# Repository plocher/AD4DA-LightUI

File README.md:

View this project on [CADLAB.io](https://cadlab.io/project/2385). 

# AD4DA-LightUI
## License: CERN Open Hardware Licence v1.2

## Status: mature

4x slide potentiometers for use with I2C-AD4DA.

The Light UI has 4x slide potentiometers which are used to control
LED Layout lighting color balances and levels. It is designed to
connect to my I2C-AD4DA (I2C 4x Analog to Digital and 1x Digital
to Analog) interface board with an RJ45/8 connection.

## Versions:
 * 1.0
 * 2.0
 * 2.1
 * 2.2

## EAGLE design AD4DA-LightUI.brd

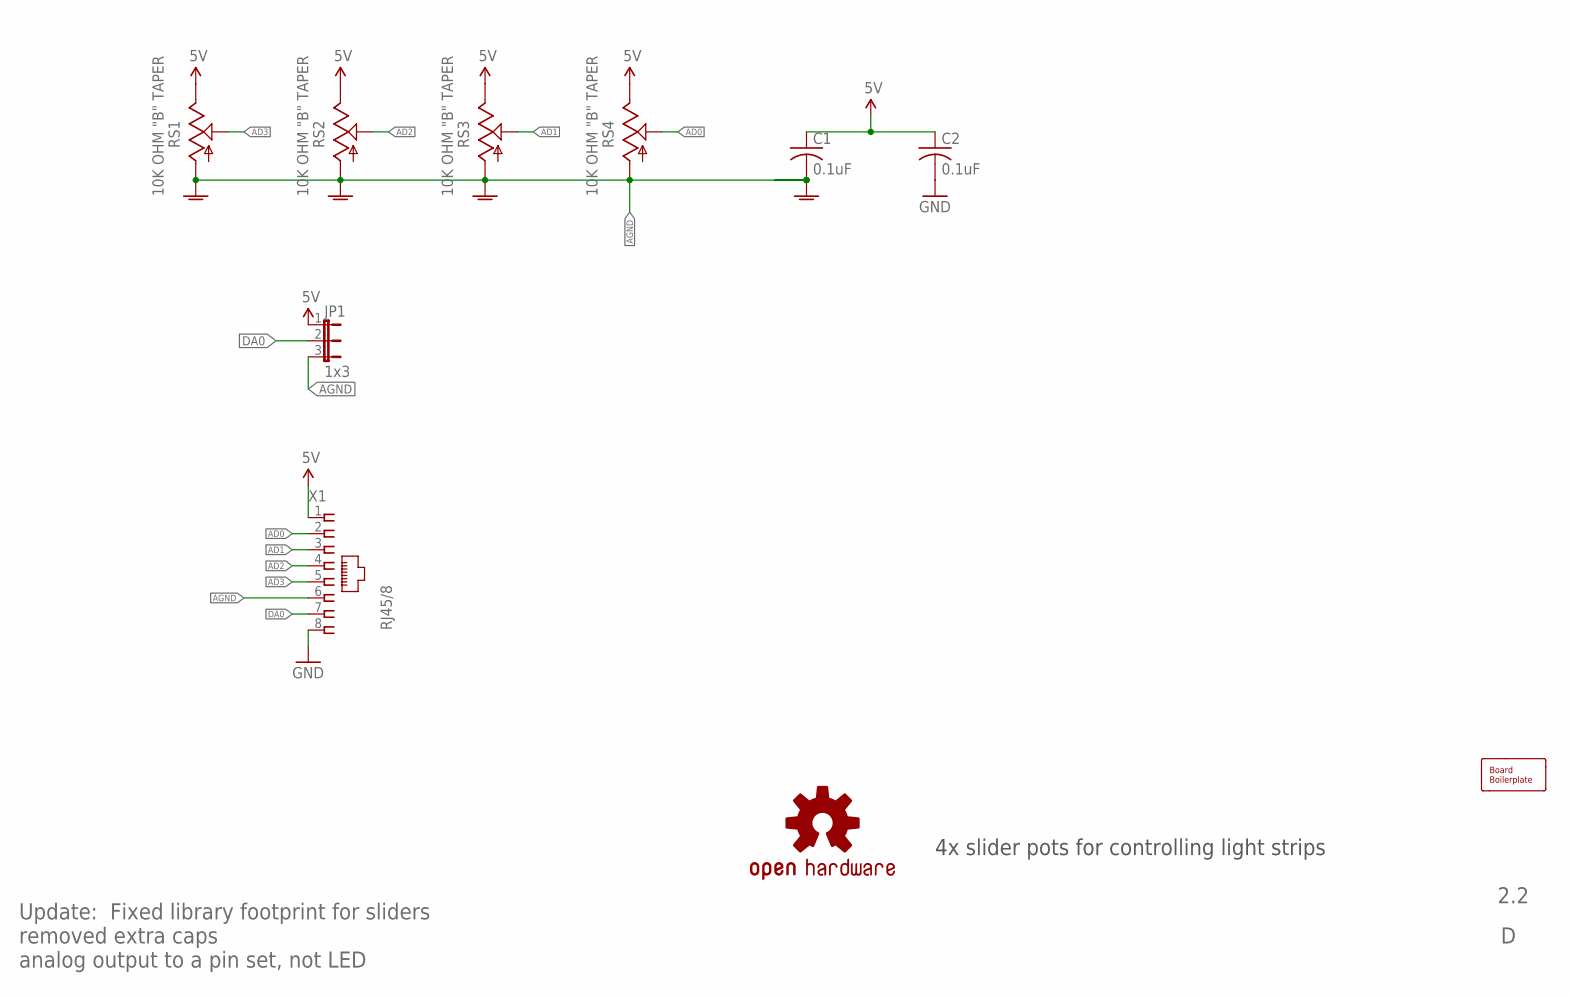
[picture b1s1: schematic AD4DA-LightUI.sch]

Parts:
BOARD1: 10x7cm; BOARD-DINRAIL-3.17INX7CM
C1, C2: 0.1uF; C050-024X044
JP1: 1x3; 1X03
LOGO1: DOC-OSHW-LOGO-L; OSHW-LOGO-L
RS1, RS2, RS3, RS4: 10K OHM "B" TAPER; SLIDER-45MM
X1: RJ45/8; RJ45-NO-SHIELD

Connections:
5V: C1.1, C2.1, JP1.1, RS1.E, RS2.E, RS3.E, RS4.E, X1.1
AD0: RS4.S, X1.2
AD1: RS3.S, X1.3
AD2: RS2.S, X1.4
AD3: RS1.S, X1.5
AGND: C1.2, JP1.3, RS1.A, RS1.AGND@0 (AGND), RS1.AGND@1 (AGND), RS2.A, RS2.AGND@0 (AGND), RS2.AGND@1 (AGND), RS3.A, RS3.AGND@0 (AGND), RS3.AGND@1 (AGND), RS4.A, RS4.AGND@0 (AGND), RS4.AGND@1 (AGND), X1.6
DA0: JP1.2, X1.7
GND: C2.2, X1.8

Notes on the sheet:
4x slider pots for controlling light strips
2.2
Update: Fixed library footprint for sliders removed extra caps analog output to a pin set, not LED

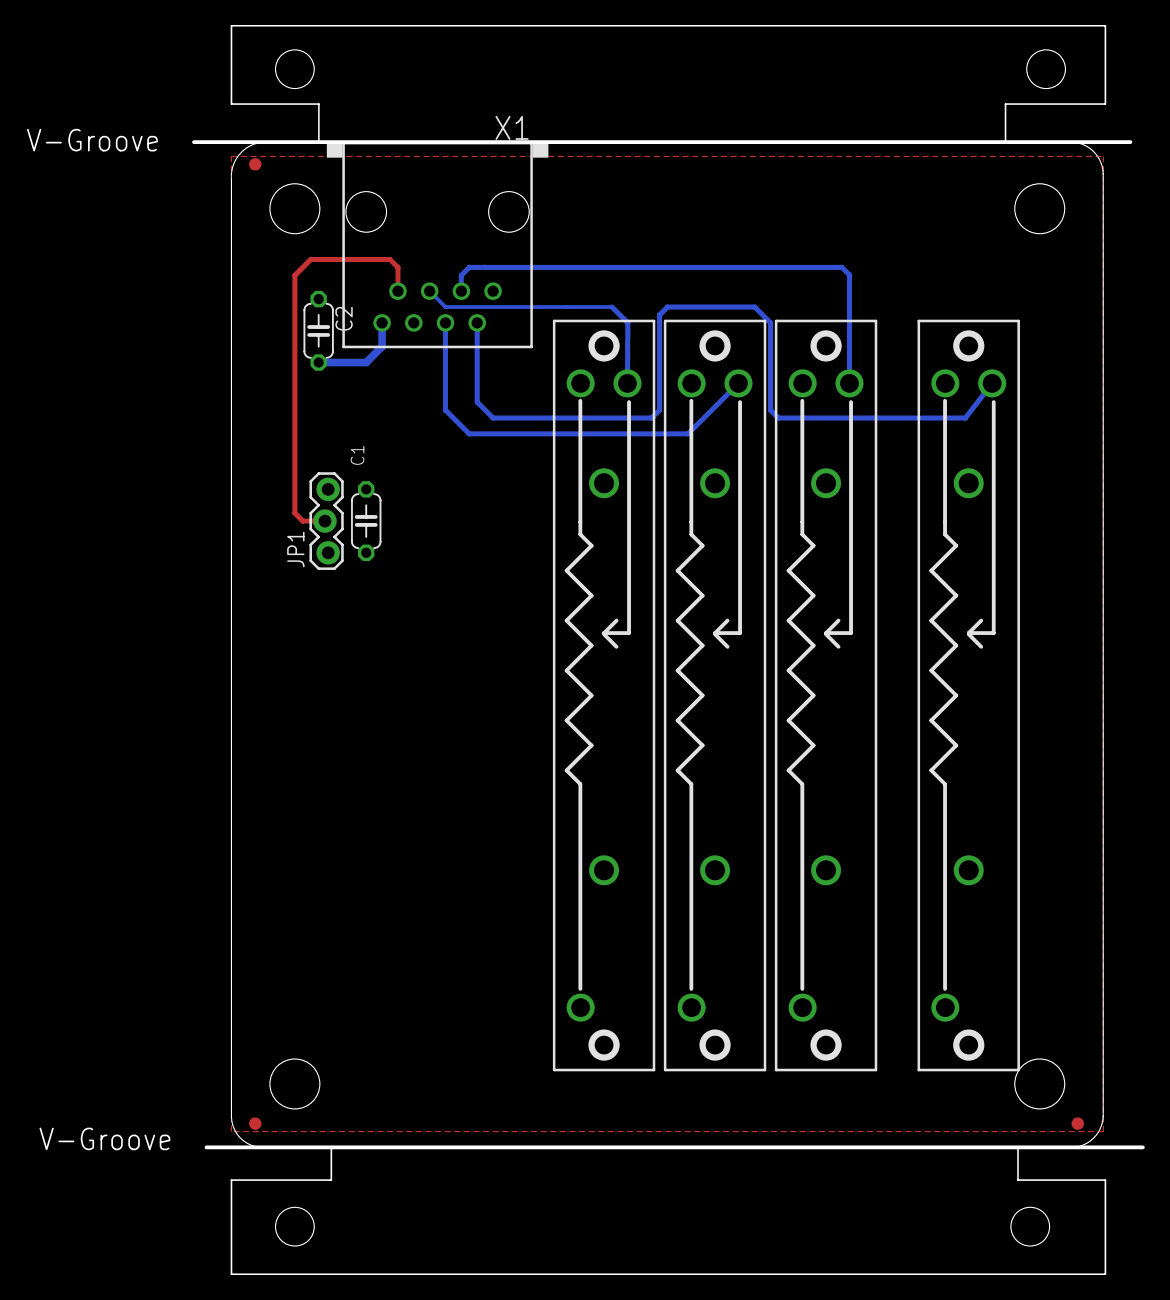
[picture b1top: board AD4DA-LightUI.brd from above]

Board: 2 copper layers, 76.0 x 100.0 mm, 10 parts (0 on the bottom side), 8 nets.

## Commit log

2019-12-07 Added graphic
2019-12-29 Backlink to CADLAB.io has been added.
2020-05-04 updated tags
2020-05-04 fixed silkscreen
2020-09-19 Obsolete

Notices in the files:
parts and their libraries:
SparkFun-Aesthetics: Licensing: CC v3.0 Share-Alike You are welcome to use this library for commercial purposes.
SPCoast: http://freedomdefined.org/OSHW Creative Commons - Attribution - ShareAlike 3.0
